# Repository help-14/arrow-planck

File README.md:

# RGB Planck
RGB Planck with arrow keys. This is a edited version of [regack's DrunkPlanck](https://geekhack.org/index.php?topic=79929.0) rev 0.6.

This should fit with all kind of case for planck.

##Layout

Support 2 arrow keys layout and three space keys layout.

[Layout 1](http://www.keyboard-layout-editor.com/#/gists/1d069f35c259fc881293490941ea733b)

[Layout 2](http://www.keyboard-layout-editor.com/#/gists/62a24cf77f6c1db29a28023afb4e101e)

[Layout 3](http://www.keyboard-layout-editor.com/#/gists/e7b004d03016d69c539ebc4d6f262bce)

Editing ...

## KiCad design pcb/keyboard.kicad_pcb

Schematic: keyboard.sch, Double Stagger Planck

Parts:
C1, C2: 22pf
C3, C4: 0.1uF; 0805
C7, C8: 1uF; 0805
G1: Graphic
H1, H2, H3, H4, H5, H6, H7, H8, H9, H10, H11, H12, H13, H14, H15: Hole
IC1: ATMEGA32U2; TQFP32
J1: USBMINI_B05
R1, R2: 22Ω; 0805
R3, R4: 10kΩ; 0805
S1: ADTSMW69NVTR; tactile_switch
X1: 7M-16.000MAAJ-T

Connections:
/Matrix/col1: IC1.6 ((OC.0B/INT0)PD0); also elsewhere on the board
/Matrix/col2: IC1.7 ((AIN0/INT1)PD1); also elsewhere on the board
/Matrix/col3: IC1.8 ((RXD1/AIN1/INT2)PD2); also elsewhere on the board
/Matrix/col4: IC1.9 ((TXD1/INT3)PD3); also elsewhere on the board
/Matrix/col5: IC1.10 ((INT5/AIN3)PD4); also elsewhere on the board
/Matrix/col6: IC1.11 ((XCK/AIN4/PCINT12)PD5); also elsewhere on the board
/Matrix/col7: IC1.12 ((~RTS~/AIN5/INT6)PD6); also elsewhere on the board
/Matrix/col8: IC1.22 ((INT4/ICP1/CLKO)PC7); also elsewhere on the board
/Matrix/col9: IC1.26 ((PCINT10)PC4); also elsewhere on the board
/Matrix/col10: IC1.5 ((PCINT11/AIN2)PC2); also elsewhere on the board
/Matrix/col11: IC1.14 ((~SS~/PCINT0)PB0); also elsewhere on the board
/Matrix/col12: IC1.15 ((SCLK/PCINT1)PB1); also elsewhere on the board
/Matrix/row1: IC1.17 ((PDO/MISO/PCINT3)PB3); also elsewhere on the board
/Matrix/row2: IC1.18 ((T1/PCINT4)PB4); also elsewhere on the board
/Matrix/row3: IC1.19 ((PCINT5)PB5); also elsewhere on the board
/Matrix/row4: IC1.20 ((PCINT6)PB6); also elsewhere on the board
/RGB/DIN: IC1.16 ((PDI/MOSI/PCINT2)PB2); also elsewhere on the board
GND: C1.2, C2.2, C3.2, C4.2, C7.2, C8.2, IC1.3 (GND), IC1.28 (UGnd), J1.5 (GND), R3.2, S1.1, X1.2, X1.4; also elsewhere on the board
unnamed: IC1.30 (D-), R1.1
unnamed: IC1.29 (D+), R2.1
unnamed: C8.1, IC1.27 (Ucap)
unnamed: IC1.13 ((~HWB~/AIN6/T0/INT7)PD7), R3.1
unnamed: IC1.24 (~RESET~(PC1/dW)), R4.2, S1.3
unnamed: J1.2 (D-), R1.2
unnamed: J1.3 (D+), R2.2
unnamed: C1.1, IC1.2 (XTAL2), X1.1
unnamed: C2.1, IC1.1 (XTAL1), X1.3
VCC: C3.1, C4.1, C7.1, IC1.4 (VCC), IC1.31 (UVcc), IC1.32 (AVCC), J1.1 (VBUS), R4.1; also elsewhere on the board

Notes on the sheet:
ATMEGA32U2 MCU Block
Reset Switch
Crystal
USB
CAPACITORS NEAR MCU
C7 NEAR USB
Double Stagger Planck Keyboard
pwm

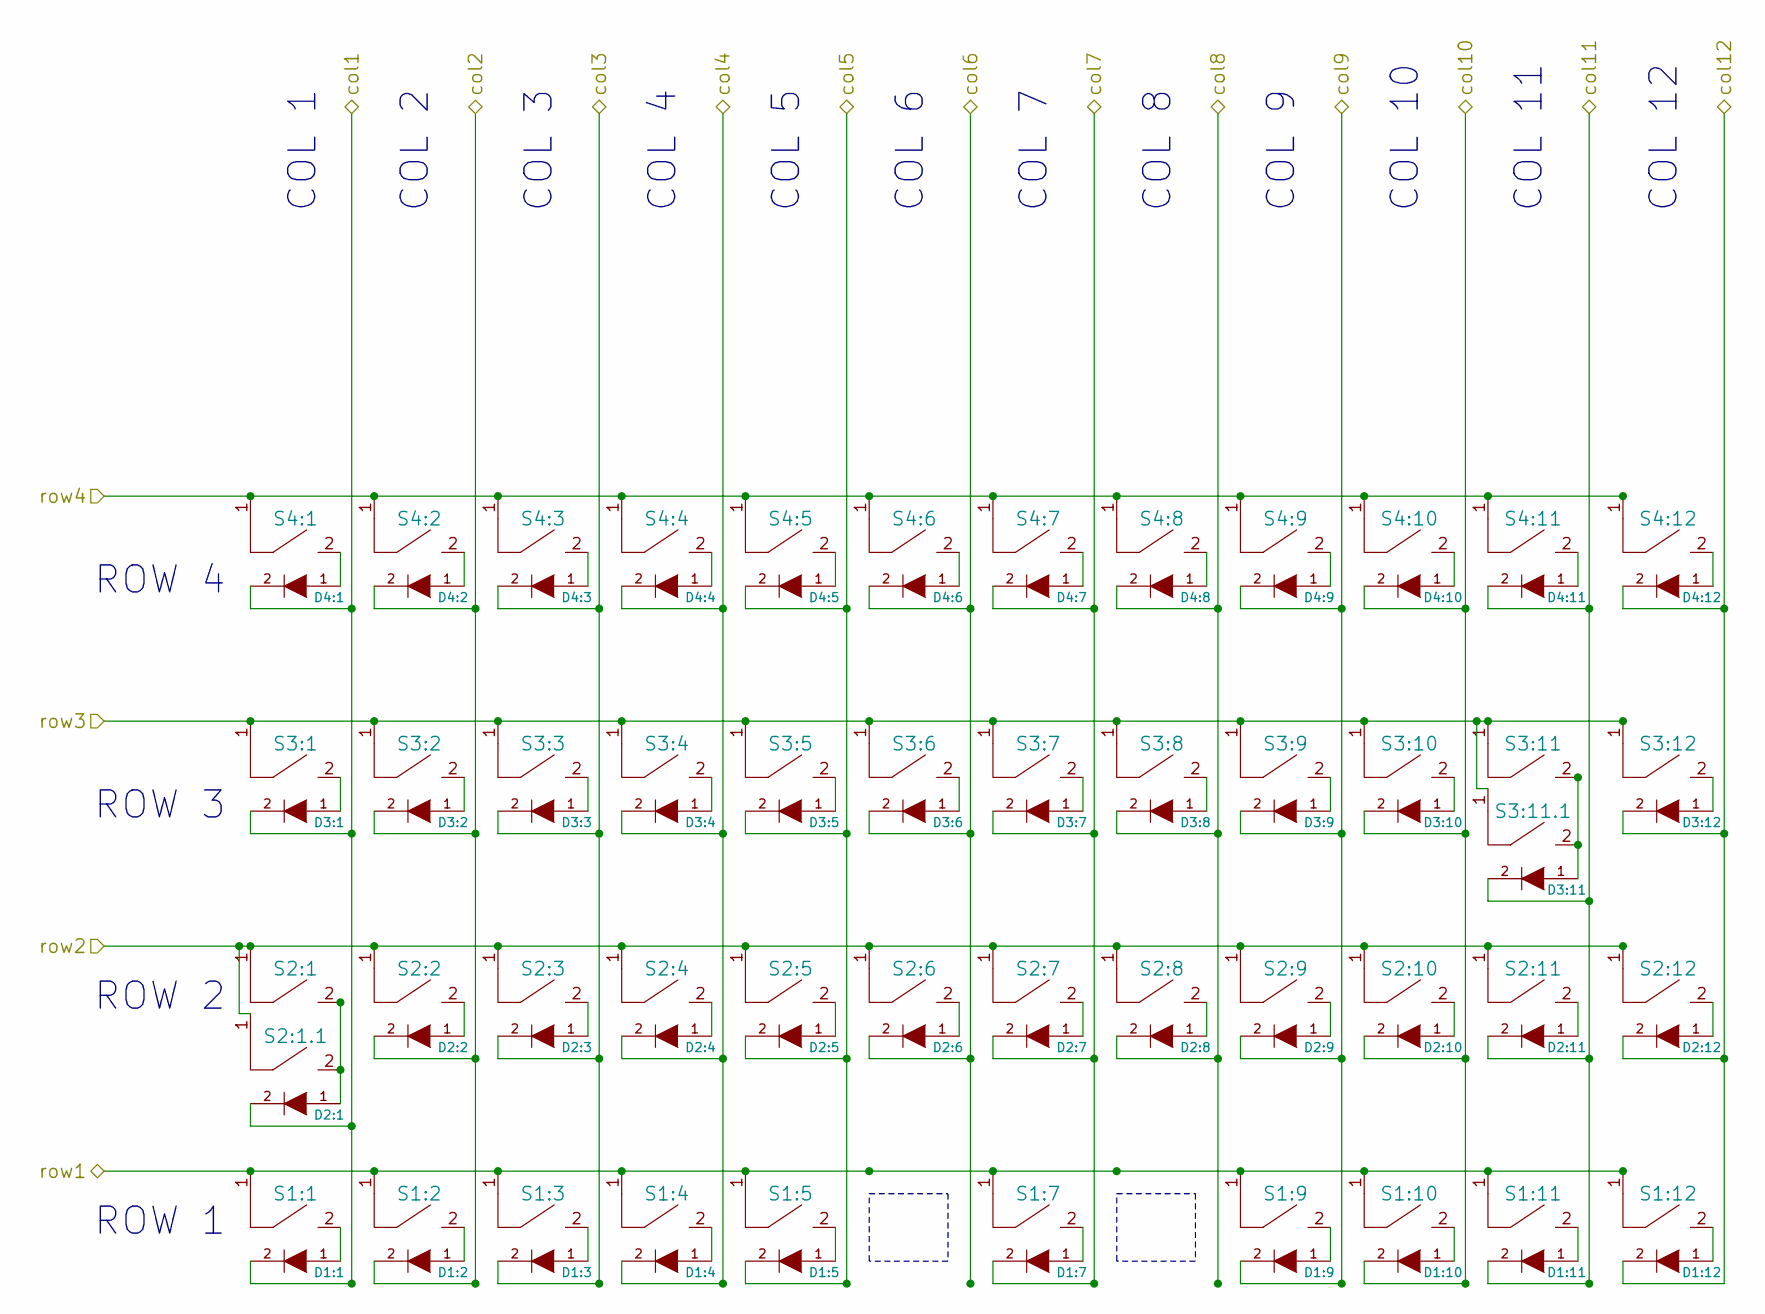
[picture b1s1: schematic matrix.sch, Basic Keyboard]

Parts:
D1:1, D1:2, D1:3, D1:4, D1:5, D1:7, D1:9, D1:10, D1:11, D1:12, D2:1, D2:2, D2:3, D2:4, D2:5, D2:6, D2:7, D2:8, D2:9, D2:10, D2:11, D2:12, D3:1, D3:2, D3:3, D3:4, D3:5, D3:6, D3:7, D3:8, D3:9, D3:10, D3:11, D3:12, D4:1, D4:2, D4:3, D4:4, D4:5, D4:6, D4:7, D4:8, D4:9, D4:10, D4:11, D4:12: 1N4148
S1:1, S1:2, S1:3, S1:4, S1:5, S1:7, S1:9, S1:10, S1:11, S1:12, S2:1, S2:1.1, S2:2, S2:3, S2:4, S2:5, S2:6, S2:7, S2:8, S2:9, S2:10, S2:11, S2:12, S3:1, S3:2, S3:3, S3:4, S3:5, S3:6, S3:7, S3:8, S3:9, S3:10, S3:11, S3:11.1, S3:12, S4:1, S4:2, S4:3, S4:4, S4:5, S4:6, S4:7, S4:8, S4:9, S4:10, S4:11, S4:12: MX1A

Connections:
/Matrix/col1: D1:1.2 (Cathode), D2:1.2 (Cathode), D3:1.2 (Cathode), D4:1.2 (Cathode); also elsewhere on the board
/Matrix/col2: D1:2.2 (Cathode), D2:2.2 (Cathode), D3:2.2 (Cathode), D4:2.2 (Cathode); also elsewhere on the board
/Matrix/col3: D1:3.2 (Cathode), D2:3.2 (Cathode), D3:3.2 (Cathode), D4:3.2 (Cathode); also elsewhere on the board
/Matrix/col4: D1:4.2 (Cathode), D2:4.2 (Cathode), D3:4.2 (Cathode), D4:4.2 (Cathode); also elsewhere on the board
/Matrix/col5: D1:5.2 (Cathode), D2:5.2 (Cathode), D3:5.2 (Cathode), D4:5.2 (Cathode); also elsewhere on the board
/Matrix/col6: D2:6.2 (Cathode), D3:6.2 (Cathode), D4:6.2 (Cathode); also elsewhere on the board
/Matrix/col7: D1:7.2 (Cathode), D2:7.2 (Cathode), D3:7.2 (Cathode), D4:7.2 (Cathode); also elsewhere on the board
/Matrix/col8: D2:8.2 (Cathode), D3:8.2 (Cathode), D4:8.2 (Cathode); also elsewhere on the board
/Matrix/col9: D1:9.2 (Cathode), D2:9.2 (Cathode), D3:9.2 (Cathode), D4:9.2 (Cathode); also elsewhere on the board
/Matrix/col10: D1:10.2 (Cathode), D2:10.2 (Cathode), D3:10.2 (Cathode), D4:10.2 (Cathode); also elsewhere on the board
/Matrix/col11: D1:11.2 (Cathode), D2:11.2 (Cathode), D3:11.2 (Cathode), D4:11.2 (Cathode); also elsewhere on the board
/Matrix/col12: D1:12.2 (Cathode), D2:12.2 (Cathode), D3:12.2 (Cathode), D4:12.2 (Cathode); also elsewhere on the board
/Matrix/row1: S1:1.1, S1:2.1, S1:3.1, S1:4.1, S1:5.1, S1:7.1, S1:9.1, S1:10.1, S1:11.1, S1:12.1; also elsewhere on the board
/Matrix/row2: S2:1.1, S2:1.1.1, S2:2.1, S2:3.1, S2:4.1, S2:5.1, S2:6.1, S2:7.1, S2:8.1, S2:9.1, S2:10.1, S2:11.1, S2:12.1; also elsewhere on the board
/Matrix/row3: S3:1.1, S3:2.1, S3:3.1, S3:4.1, S3:5.1, S3:6.1, S3:7.1, S3:8.1, S3:9.1, S3:10.1, S3:11.1, S3:11.1.1, S3:12.1; also elsewhere on the board
/Matrix/row4: S4:1.1, S4:2.1, S4:3.1, S4:4.1, S4:5.1, S4:6.1, S4:7.1, S4:8.1, S4:9.1, S4:10.1, S4:11.1, S4:12.1; also elsewhere on the board
unnamed: D4:9.1 (Anode), S4:9.2
unnamed: D3:10.1 (Anode), S3:10.2
unnamed: D4:10.1 (Anode), S4:10.2
unnamed: D4:11.1 (Anode), S4:11.2
unnamed 31: D2:11.1 (Anode), S2:11.2; also elsewhere on the board
unnamed 32: D2:10.1 (Anode), S2:10.2; also elsewhere on the board
unnamed: D1:11.1 (Anode), S1:11.2
unnamed: D2:9.1 (Anode), S2:9.2
unnamed: D3:9.1 (Anode), S3:9.2
unnamed: D4:8.1 (Anode), S4:8.2
unnamed: D4:7.1 (Anode), S4:7.2
unnamed: D4:5.1 (Anode), S4:5.2
unnamed: D4:4.1 (Anode), S4:4.2
unnamed: D3:4.1 (Anode), S3:4.2
unnamed: D2:4.1 (Anode), S2:4.2
unnamed: D4:6.1 (Anode), S4:6.2
unnamed: D3:6.1 (Anode), S3:6.2
unnamed: D2:5.1 (Anode), S2:5.2
unnamed: D3:8.1 (Anode), S3:8.2
unnamed: D2:8.1 (Anode), S2:8.2
unnamed: D2:7.1 (Anode), S2:7.2
unnamed: D3:7.1 (Anode), S3:7.2
unnamed: D3:5.1 (Anode), S3:5.2
unnamed: D1:1.1 (Anode), S1:1.2
unnamed: D1:10.1 (Anode), S1:10.2
unnamed: D3:12.1 (Anode), S3:12.2
unnamed: D4:12.1 (Anode), S4:12.2
unnamed 54: D2:12.1 (Anode), S2:12.2; also elsewhere on the board
unnamed: D2:1.1 (Anode), S2:1.2, S2:1.1.2
unnamed: D3:11.1 (Anode), S3:11.2, S3:11.1.2
unnamed: D3:1.1 (Anode), S3:1.2
unnamed 58: D1:9.1 (Anode), S1:9.2; also elsewhere on the board
unnamed: D1:12.1 (Anode), S1:12.2
unnamed: D1:5.1 (Anode), S1:5.2
unnamed: D1:4.1 (Anode), S1:4.2
unnamed: D4:1.1 (Anode), S4:1.2
unnamed: D3:3.1 (Anode), S3:3.2
unnamed: D3:2.1 (Anode), S3:2.2
unnamed: D2:6.1 (Anode), S2:6.2
unnamed: D1:7.1 (Anode), S1:7.2
unnamed: D1:3.1 (Anode), S1:3.2
unnamed: D1:2.1 (Anode), S1:2.2
unnamed: D2:3.1 (Anode), S2:3.2
unnamed: D2:2.1 (Anode), S2:2.2
unnamed: D4:3.1 (Anode), S4:3.2
unnamed: D4:2.1 (Anode), S4:2.2

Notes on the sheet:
ROW 1
ROW 2
ROW 3
ROW 4
COL 1
COL 2
COL 3
COL 4
COL 5
COL 6
COL 7
COL 8
COL 9
COL 10
COL 11
COL 12

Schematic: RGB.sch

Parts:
C1:1, C1:2, C1:3, C1:4, C1:5, C1:7, C1:9, C1:10, C1:11, C1:12, C2:1, C2:2, C2:3, C2:4, C2:5, C2:6, C2:7, C2:8, C2:9, C2:10, C2:11, C2:12, C3:1, C3:2, C3:3, C3:4, C3:5, C3:6, C3:7, C3:8, C3:9, C3:10, C3:11, C3:12, C4:1, C4:2, C4:3, C4:4, C4:5, C4:6, C4:7, C4:8, C4:9, C4:10, C4:11, C4:12: 0.1uF 50v
IC1:1, IC1:2, IC1:3, IC1:4, IC1:5, IC1:7, IC1:9, IC1:10, IC1:11, IC1:12, IC2:1, IC2:2, IC2:3, IC2:4, IC2:5, IC2:6, IC2:7, IC2:8, IC2:9, IC2:10, IC2:11, IC2:12, IC3:1, IC3:2, IC3:3, IC3:4, IC3:5, IC3:6, IC3:7, IC3:8, IC3:9, IC3:10, IC3:11, IC3:12, IC4:1, IC4:2, IC4:3, IC4:4, IC4:5, IC4:6, IC4:7, IC4:8, IC4:9, IC4:10, IC4:11, IC4:12: WS2811
L1:1, L1:2, L1:3, L1:4, L1:5, L1:7, L1:9, L1:10, L1:11, L1:12, L2:1, L2:1.1, L2:2, L2:3, L2:4, L2:5, L2:6, L2:7, L2:8, L2:9, L2:10, L2:11, L2:12, L3:1, L3:2, L3:3, L3:4, L3:5, L3:6, L3:7, L3:8, L3:9, L3:10, L3:11, L3:11.1, L3:12, L4:1, L4:2, L4:3, L4:4, L4:5, L4:6, L4:7, L4:8, L4:9, L4:10, L4:11, L4:12: 0606_RGB_LED
R1:1, R1:2, R1:3, R1:4, R1:5, R1:7, R1:9, R1:10, R1:11, R1:12, R2:1, R2:2, R2:3, R2:4, R2:5, R2:6, R2:7, R2:8, R2:9, R2:10, R2:11, R2:12, R3:1, R3:2, R3:3, R3:4, R3:5, R3:6, R3:7, R3:8, R3:9, R3:10, R3:11, R3:12, R4:1, R4:2, R4:3, R4:4, R4:5, R4:6, R4:7, R4:8, R4:9, R4:10, R4:11, R4:12: 100
RBL1: 33

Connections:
/RGB/DIN: RBL1.2; also elsewhere on the board
GND: C1:1.2, C1:2.2, C1:3.2, C1:4.2, C1:5.2, C1:7.2, C1:9.2, C1:10.2, C1:11.2, C1:12.2, C2:1.2, C2:2.2, C2:3.2, C2:4.2, C2:5.2, C2:6.2, C2:7.2, C2:8.2, C2:9.2, C2:10.2, C2:11.2, C2:12.2, C3:1.2, C3:2.2, C3:3.2, C3:4.2, C3:5.2, C3:6.2, C3:7.2, C3:8.2, C3:9.2, C3:10.2, C3:11.2, C3:12.2, C4:1.2, C4:2.2, C4:3.2, C4:4.2, C4:5.2, C4:6.2, C4:7.2, C4:8.2, C4:9.2, C4:10.2, C4:11.2, C4:12.2, IC1:1.4 (GND), IC1:2.4 (GND), IC1:3.4 (GND), IC1:4.4 (GND), IC1:5.4 (GND), IC1:7.4 (GND), IC1:9.4 (GND), IC1:10.4 (GND), IC1:11.4 (GND), IC1:12.4 (GND), IC2:1.4 (GND), IC2:2.4 (GND), IC2:3.4 (GND), IC2:4.4 (GND), IC2:5.4 (GND), IC2:6.4 (GND), IC2:7.4 (GND), IC2:8.4 (GND), IC2:9.4 (GND), IC2:10.4 (GND), IC2:11.4 (GND), IC2:12.4 (GND), IC3:1.4 (GND), IC3:2.4 (GND), IC3:3.4 (GND), IC3:4.4 (GND), IC3:5.4 (GND), IC3:6.4 (GND), IC3:7.4 (GND), IC3:8.4 (GND), IC3:9.4 (GND), IC3:10.4 (GND), IC3:11.4 (GND), IC3:12.4 (GND), IC4:1.4 (GND), IC4:2.4 (GND), IC4:3.4 (GND), IC4:4.4 (GND), IC4:5.4 (GND), IC4:6.4 (GND), IC4:7.4 (GND), IC4:8.4 (GND), IC4:9.4 (GND), IC4:10.4 (GND), IC4:11.4 (GND), IC4:12.4 (GND); also elsewhere on the board
unnamed: IC4:10.2 (OutG), L4:10.2 (G)
unnamed: IC4:10.3 (OutB), L4:10.3 (B)
unnamed: IC4:10.1 (OutR), L4:10.1 (R)
unnamed: IC1:9.5 (Dout), IC4:10.6 (Din)
unnamed: C4:10.1, IC4:10.8 (Vcc), R4:10.1
unnamed: IC3:9.6 (Din), IC4:9.5 (Dout)
unnamed: IC2:9.6 (Din), IC3:9.5 (Dout)
unnamed: IC3:10.2 (OutG), L3:10.2 (G)
unnamed: IC3:10.6 (Din), IC4:10.5 (Dout)
unnamed: IC2:10.6 (Din), IC3:10.5 (Dout)
unnamed: IC3:10.3 (OutB), L3:10.3 (B)
unnamed: IC3:10.1 (OutR), L3:10.1 (R)
unnamed: C3:10.1, IC3:10.8 (Vcc), R3:10.1
unnamed: IC1:9.6 (Din), IC2:9.5 (Dout)
unnamed: C1:9.1, IC1:9.8 (Vcc), R1:9.1
unnamed 88: IC1:9.3 (OutB), L1:9.3 (B); also elsewhere on the board
unnamed 89: IC1:9.2 (OutG), L1:9.2 (G); also elsewhere on the board
unnamed 90: IC1:9.1 (OutR), L1:9.1 (R); also elsewhere on the board
unnamed: IC4:11.2 (OutG), L4:11.2 (G)
unnamed: C4:9.1, IC4:9.8 (Vcc), R4:9.1
unnamed: C2:9.1, IC2:9.8 (Vcc), R2:9.1
unnamed: C3:9.1, IC3:9.8 (Vcc), R3:9.1
unnamed: C2:10.1, IC2:10.8 (Vcc), R2:10.1
unnamed: IC1:10.6 (Din), IC2:10.5 (Dout)
unnamed: IC4:11.1 (OutR), L4:11.1 (R)
unnamed: IC4:11.3 (OutB), L4:11.3 (B)
unnamed: IC1:10.5 (Dout), IC4:11.6 (Din)
unnamed: C1:10.1, IC1:10.8 (Vcc), R1:10.1
unnamed: IC2:10.2 (OutG), L2:10.2 (G)
unnamed: IC2:10.3 (OutB), L2:10.3 (B)
unnamed: IC2:10.1 (OutR), L2:10.1 (R)
unnamed: IC1:10.1 (OutR), L1:10.1 (R)
unnamed: IC1:10.3 (OutB), L1:10.3 (B)
unnamed: IC1:10.2 (OutG), L1:10.2 (G)
unnamed: IC3:8.2 (OutG), L3:8.2 (G)
unnamed: IC3:8.3 (OutB), L3:8.3 (B)
unnamed: IC3:8.1 (OutR), L3:8.1 (R)
unnamed: C3:8.1, IC3:8.8 (Vcc), R3:8.1
unnamed: IC2:8.3 (OutB), L2:8.3 (B)
unnamed: C2:8.1, IC2:8.8 (Vcc), R2:8.1
unnamed: IC2:8.6 (Din), IC3:8.5 (Dout)
unnamed: IC2:8.2 (OutG), L2:8.2 (G)
unnamed: IC2:8.1 (OutR), L2:8.1 (R)
unnamed: C3:7.1, IC3:7.8 (Vcc), R3:7.1
unnamed: IC1:7.5 (Dout), IC4:8.6 (Din)
unnamed: IC3:7.6 (Din), IC4:7.5 (Dout)
unnamed: IC2:7.6 (Din), IC3:7.5 (Dout)
unnamed: C2:7.1, IC2:7.8 (Vcc), R2:7.1
unnamed: C4:7.1, IC4:7.8 (Vcc), R4:7.1
unnamed: IC1:7.6 (Din), IC2:7.5 (Dout)
unnamed: IC4:8.3 (OutB), L4:8.3 (B)
unnamed: C4:8.1, IC4:8.8 (Vcc), R4:8.1
unnamed: IC3:8.6 (Din), IC4:8.5 (Dout)
unnamed: IC4:8.2 (OutG), L4:8.2 (G)
unnamed: IC4:8.1 (OutR), L4:8.1 (R)
unnamed: IC3:9.3 (OutB), L3:9.3 (B)
unnamed: IC3:9.2 (OutG), L3:9.2 (G)
unnamed: IC3:9.1 (OutR), L3:9.1 (R)
unnamed: IC2:9.3 (OutB), L2:9.3 (B)
unnamed: IC2:9.2 (OutG), L2:9.2 (G)
unnamed: IC2:9.1 (OutR), L2:9.1 (R)
unnamed: IC2:8.5 (Dout), IC4:9.6 (Din)
unnamed: IC4:9.3 (OutB), L4:9.3 (B)
unnamed: IC4:9.2 (OutG), L4:9.2 (G)
unnamed: IC4:9.1 (OutR), L4:9.1 (R)
unnamed: IC2:6.5 (Dout), IC4:7.6 (Din)
unnamed: IC3:12.6 (Din), IC4:12.5 (Dout)
unnamed: C1:3.1, IC1:3.8 (Vcc), R1:3.1
unnamed: IC1:3.2 (OutG), L1:3.2 (G)
unnamed: IC1:3.1 (OutR), L1:3.1 (R)
unnamed: IC1:3.3 (OutB), L1:3.3 (B)
unnamed: IC2:12.6 (Din), IC3:12.5 (Dout)
unnamed: IC1:11.5 (Dout), IC4:12.6 (Din)
unnamed: IC1:12.6 (Din), IC2:12.5 (Dout)
unnamed: C1:12.1, IC1:12.8 (Vcc), R1:12.1
unnamed: IC1:12.3 (OutB), L1:12.3 (B)
unnamed: IC1:12.2 (OutG), L1:12.2 (G)
unnamed: IC1:12.1 (OutR), L1:12.1 (R)
unnamed: C2:12.1, IC2:12.8 (Vcc), R2:12.1
unnamed: C4:12.1, IC4:12.8 (Vcc), R4:12.1
unnamed: C3:12.1, IC3:12.8 (Vcc), R3:12.1
unnamed: IC2:1.3 (OutB), L2:1.3 (B), L2:1.1.3 (B)
unnamed: IC2:1.2 (OutG), L2:1.2 (G), L2:1.1.2 (G)
unnamed: IC2:1.1 (OutR), L2:1.1 (R), L2:1.1.1 (R)
unnamed: IC3:6.3 (OutB), L3:6.3 (B)
unnamed: IC3:6.2 (OutG), L3:6.2 (G)
unnamed: IC3:6.1 (OutR), L3:6.1 (R)
unnamed: IC3:11.2 (OutG), L3:11.2 (G), L3:11.1.2 (G)
unnamed: IC3:11.3 (OutB), L3:11.3 (B), L3:11.1.3 (B)
unnamed: IC3:11.1 (OutR), L3:11.1 (R), L3:11.1.1 (R)
unnamed: IC1:2.1 (OutR), L1:2.1 (R)
unnamed: IC1:2.2 (OutG), L1:2.2 (G)
unnamed: IC1:3.6 (Din), IC2:3.5 (Dout)
unnamed: C1:2.1, IC1:2.8 (Vcc), R1:2.1
unnamed: IC1:2.5 (Dout), IC4:3.6 (Din)
unnamed: IC1:2.3 (OutB), L1:2.3 (B)
unnamed: IC1:11.1 (OutR), L1:11.1 (R)
unnamed: IC1:11.3 (OutB), L1:11.3 (B)
unnamed: IC1:11.2 (OutG), L1:11.2 (G)
unnamed: IC1:11.6 (Din), IC2:11.5 (Dout)
unnamed: IC2:11.3 (OutB), L2:11.3 (B)
unnamed: IC2:11.2 (OutG), L2:11.2 (G)
unnamed: C1:11.1, IC1:11.8 (Vcc), R1:11.1
unnamed: C4:11.1, IC4:11.8 (Vcc), R4:11.1
unnamed: IC2:11.1 (OutR), L2:11.1 (R)
unnamed: C2:11.1, IC2:11.8 (Vcc), R2:11.1
unnamed: C3:11.1, IC3:11.8 (Vcc), R3:11.1
unnamed: IC3:11.6 (Din), IC4:11.5 (Dout)
unnamed: IC2:11.6 (Din), IC3:11.5 (Dout)
unnamed: IC3:12.3 (OutB), L3:12.3 (B)
unnamed: IC3:12.2 (OutG), L3:12.2 (G)
unnamed: IC3:12.1 (OutR), L3:12.1 (R)
unnamed: IC2:12.3 (OutB), L2:12.3 (B)
unnamed: IC2:12.2 (OutG), L2:12.2 (G)
unnamed: IC2:12.1 (OutR), L2:12.1 (R)
unnamed: IC4:12.3 (OutB), L4:12.3 (B)
unnamed: IC4:12.2 (OutG), L4:12.2 (G)
unnamed: IC4:12.1 (OutR), L4:12.1 (R)
unnamed: C1:4.1, IC1:4.8 (Vcc), R1:4.1
unnamed: IC3:2.6 (Din), IC4:2.5 (Dout)
unnamed: IC2:2.6 (Din), IC3:2.5 (Dout)
unnamed: C2:2.1, IC2:2.8 (Vcc), R2:2.1
unnamed: C4:2.1, IC4:2.8 (Vcc), R4:2.1
unnamed: C3:2.1, IC3:2.8 (Vcc), R3:2.1
unnamed: C3:3.1, IC3:3.8 (Vcc), R3:3.1
unnamed: C4:3.1, IC4:3.8 (Vcc), R4:3.1
unnamed: IC4:3.3 (OutB), L4:3.3 (B)
unnamed: IC4:3.2 (OutG), L4:3.2 (G)
unnamed: IC4:3.1 (OutR), L4:3.1 (R)
unnamed: IC1:4.1 (OutR), L1:4.1 (R)
unnamed: IC1:4.3 (OutB), L1:4.3 (B)
unnamed: IC1:4.2 (OutG), L1:4.2 (G)
unnamed: IC1:2.6 (Din), IC2:2.5 (Dout)
unnamed: IC2:2.3 (OutB), L2:2.3 (B)
unnamed: IC1:5.6 (Din), IC2:5.5 (Dout)
unnamed: C1:5.1, IC1:5.8 (Vcc), R1:5.1
unnamed: IC1:5.3 (OutB), L1:5.3 (B)
unnamed: IC1:5.2 (OutG), L1:5.2 (G)
unnamed: IC1:5.1 (OutR), L1:5.1 (R)
unnamed: IC2:3.6 (Din), IC3:3.5 (Dout)
unnamed: C2:3.1, IC2:3.8 (Vcc), R2:3.1
unnamed: IC3:3.6 (Din), IC4:3.5 (Dout)
unnamed: IC3:3.3 (OutB), L3:3.3 (B)
unnamed: IC3:3.2 (OutG), L3:3.2 (G)
unnamed: IC3:3.1 (OutR), L3:3.1 (R)
unnamed: IC2:2.2 (OutG), L2:2.2 (G)
unnamed: IC2:3.3 (OutB), L2:3.3 (B)
unnamed: IC2:3.2 (OutG), L2:3.2 (G)
unnamed: IC2:3.1 (OutR), L2:3.1 (R)
unnamed: C2:1.1, IC2:1.8 (Vcc), R2:1.1
unnamed: IC1:1.3 (OutB), L1:1.3 (B)
unnamed: IC1:1.6 (Din), IC2:1.5 (Dout)
unnamed: IC1:1.2 (OutG), L1:1.2 (G)
unnamed: IC1:1.1 (OutR), L1:1.1 (R)
unnamed: C1:1.1, IC1:1.8 (Vcc), R1:1.1
unnamed: IC4:1.3 (OutB), L4:1.3 (B)
unnamed: IC4:1.2 (OutG), L4:1.2 (G)
unnamed: IC4:1.1 (OutR), L4:1.1 (R)
unnamed: C4:1.1, IC4:1.8 (Vcc), R4:1.1
unnamed: IC4:1.6 (Din), RBL1.1
unnamed: IC3:1.3 (OutB), L3:1.3 (B)
unnamed: IC3:1.6 (Din), IC4:1.5 (Dout)
unnamed: IC2:1.6 (Din), IC3:1.5 (Dout)
unnamed: IC3:1.2 (OutG), L3:1.2 (G)
unnamed: IC3:1.1 (OutR), L3:1.1 (R)
unnamed: C3:1.1, IC3:1.8 (Vcc), R3:1.1
unnamed: IC3:2.2 (OutG), L3:2.2 (G)
unnamed: IC3:2.1 (OutR), L3:2.1 (R)
unnamed: IC3:2.3 (OutB), L3:2.3 (B)
unnamed: IC1:1.5 (Dout), IC4:2.6 (Din)
unnamed: IC2:2.1 (OutR), L2:2.1 (R)
unnamed: IC4:2.3 (OutB), L4:2.3 (B)
unnamed: IC4:2.2 (OutG), L4:2.2 (G)
unnamed: IC4:2.1 (OutR), L4:2.1 (R)
unnamed: C3:6.1, IC3:6.8 (Vcc), R3:6.1
unnamed: IC1:5.5 (Dout), IC4:6.6 (Din)
unnamed: IC3:6.6 (Din), IC4:6.5 (Dout)
unnamed: IC2:6.6 (Din), IC3:6.5 (Dout)
unnamed: IC2:6.3 (OutB), L2:6.3 (B)
unnamed: IC2:6.2 (OutG), L2:6.2 (G)
unnamed: IC2:6.1 (OutR), L2:6.1 (R)
unnamed: C2:6.1, IC2:6.8 (Vcc), R2:6.1
unnamed: C4:5.1, IC4:5.8 (Vcc), R4:5.1
unnamed: C2:5.1, IC2:5.8 (Vcc), R2:5.1
unnamed: C3:5.1, IC3:5.8 (Vcc), R3:5.1
unnamed: IC4:6.3 (OutB), L4:6.3 (B)
unnamed: IC4:6.2 (OutG), L4:6.2 (G)
unnamed: IC4:6.1 (OutR), L4:6.1 (R)
unnamed: C4:6.1, IC4:6.8 (Vcc), R4:6.1
unnamed: IC3:5.6 (Din), IC4:5.5 (Dout)
unnamed: IC2:5.6 (Din), IC3:5.5 (Dout)
unnamed: C1:7.1, IC1:7.8 (Vcc), R1:7.1
unnamed: IC3:7.1 (OutR), L3:7.1 (R)
unnamed: IC3:7.3 (OutB), L3:7.3 (B)
unnamed: IC3:7.2 (OutG), L3:7.2 (G)
unnamed: IC2:7.2 (OutG), L2:7.2 (G)
unnamed: IC2:7.3 (OutB), L2:7.3 (B)
unnamed: IC2:7.1 (OutR), L2:7.1 (R)
unnamed: IC4:7.2 (OutG), L4:7.2 (G)
unnamed: IC4:7.3 (OutB), L4:7.3 (B)
unnamed: IC4:7.1 (OutR), L4:7.1 (R)
unnamed: IC2:4.1 (OutR), L2:4.1 (R)
unnamed: IC1:4.6 (Din), IC2:4.5 (Dout)
unnamed: IC2:4.3 (OutB), L2:4.3 (B)
unnamed: IC2:4.2 (OutG), L2:4.2 (G)
unnamed: C2:4.1, IC2:4.8 (Vcc), R2:4.1
unnamed: C4:4.1, IC4:4.8 (Vcc), R4:4.1
unnamed: C3:4.1, IC3:4.8 (Vcc), R3:4.1
unnamed: IC4:4.1 (OutR), L4:4.1 (R)
unnamed: IC1:3.5 (Dout), IC4:4.6 (Din)
unnamed: IC4:4.3 (OutB), L4:4.3 (B)
unnamed: IC4:4.2 (OutG), L4:4.2 (G)
unnamed: IC3:4.1 (OutR), L3:4.1 (R)
unnamed: IC3:4.6 (Din), IC4:4.5 (Dout)
unnamed: IC2:4.6 (Din), IC3:4.5 (Dout)
unnamed: IC3:4.3 (OutB), L3:4.3 (B)
unnamed: IC3:4.2 (OutG), L3:4.2 (G)
unnamed: IC2:5.2 (OutG), L2:5.2 (G)
unnamed: IC2:5.3 (OutB), L2:5.3 (B)
unnamed: IC2:5.1 (OutR), L2:5.1 (R)
unnamed: IC1:7.2 (OutG), L1:7.2 (G)
unnamed: IC1:7.3 (OutB), L1:7.3 (B)
unnamed: IC1:7.1 (OutR), L1:7.1 (R)
unnamed: IC4:5.3 (OutB), L4:5.3 (B)
unnamed: IC1:4.5 (Dout), IC4:5.6 (Din)
unnamed: IC4:5.2 (OutG), L4:5.2 (G)
unnamed: IC4:5.1 (OutR), L4:5.1 (R)
unnamed: IC3:5.2 (OutG), L3:5.2 (G)
unnamed: IC3:5.3 (OutB), L3:5.3 (B)
unnamed: IC3:5.1 (OutR), L3:5.1 (R)
VCC: L1:1.4 (Vcc), L1:2.4 (Vcc), L1:3.4 (Vcc), L1:4.4 (Vcc), L1:5.4 (Vcc), L1:7.4 (Vcc), L1:9.4 (Vcc), L1:10.4 (Vcc), L1:11.4 (Vcc), L1:12.4 (Vcc), L2:1.4 (Vcc), L2:1.1.4 (Vcc), L2:2.4 (Vcc), L2:3.4 (Vcc), L2:4.4 (Vcc), L2:5.4 (Vcc), L2:6.4 (Vcc), L2:7.4 (Vcc), L2:8.4 (Vcc), L2:9.4 (Vcc), L2:10.4 (Vcc), L2:11.4 (Vcc), L2:12.4 (Vcc), L3:1.4 (Vcc), L3:2.4 (Vcc), L3:3.4 (Vcc), L3:4.4 (Vcc), L3:5.4 (Vcc), L3:6.4 (Vcc), L3:7.4 (Vcc), L3:8.4 (Vcc), L3:9.4 (Vcc), L3:10.4 (Vcc), L3:11.4 (Vcc), L3:11.1.4 (Vcc), L3:12.4 (Vcc), L4:1.4 (Vcc), L4:2.4 (Vcc), L4:3.4 (Vcc), L4:4.4 (Vcc), L4:5.4 (Vcc), L4:6.4 (Vcc), L4:7.4 (Vcc), L4:8.4 (Vcc), L4:9.4 (Vcc), L4:10.4 (Vcc), L4:11.4 (Vcc), L4:12.4 (Vcc), R1:1.2, R1:2.2, R1:3.2, R1:4.2, R1:5.2, R1:7.2, R1:9.2, R1:10.2, R1:11.2, R1:12.2, R2:1.2, R2:2.2, R2:3.2, R2:4.2, R2:5.2, R2:6.2, R2:7.2, R2:8.2, R2:9.2, R2:10.2, R2:11.2, R2:12.2, R3:1.2, R3:2.2, R3:3.2, R3:4.2, R3:5.2, R3:6.2, R3:7.2, R3:8.2, R3:9.2, R3:10.2, R3:11.2, R3:12.2, R4:1.2, R4:2.2, R4:3.2, R4:4.2, R4:5.2, R4:6.2, R4:7.2, R4:8.2, R4:9.2, R4:10.2, R4:11.2, R4:12.2; also elsewhere on the board

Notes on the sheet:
ROW 4
ROW 3
ROW 2
ROW 1
COL 1
COL 2
COL 3
COL 4
COL 5
COL 6
COL 7
COL 8
COL 9
COL 10
COL 11
COL 12
NO SWITCH

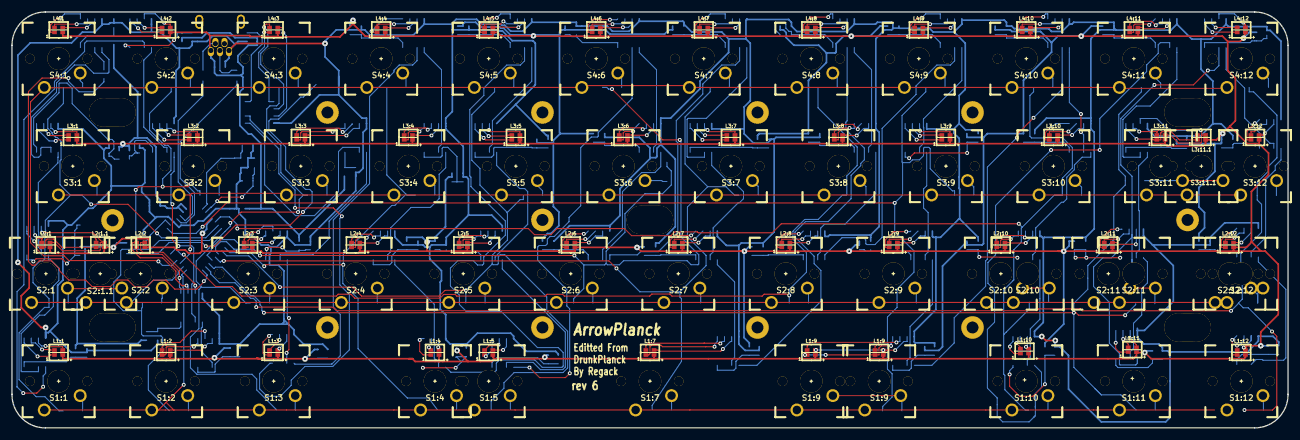
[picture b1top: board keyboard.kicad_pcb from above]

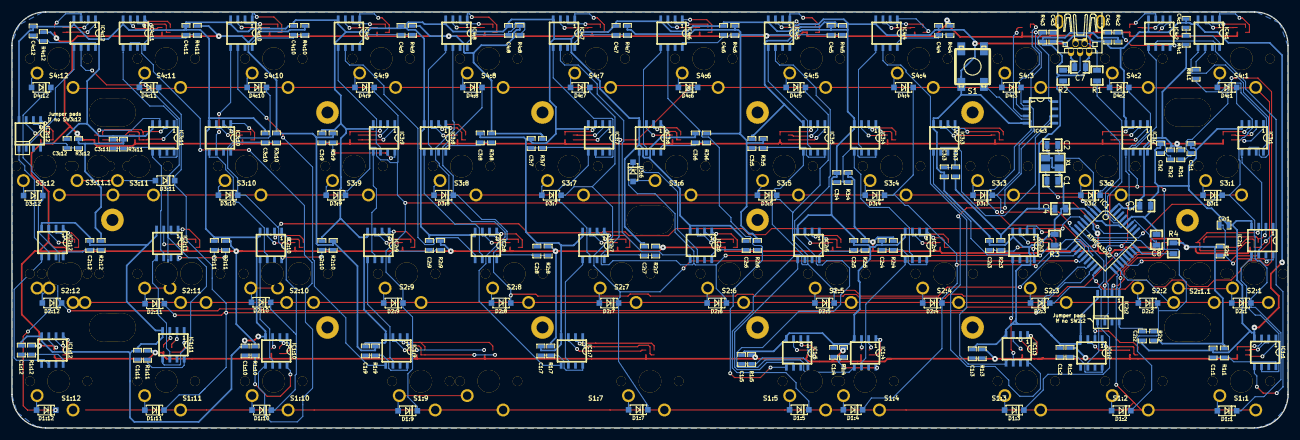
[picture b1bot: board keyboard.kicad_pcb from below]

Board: 2 copper layers, 225.5 x 73.5 mm, 326 parts (199 on the bottom side), 304 nets.

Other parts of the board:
H1.1, H1.2, H2.1, H2.2, H3.1, H3.2, H4.1, H4.2, H5.1, H5.2, H16: HOLE; Mechanical_Hole
L1:9#2: 0606_RGB_LED; CHERRY_MX_RGBLED
S1:9#2, S2:12#2: MX1A; CHERRY_PCB_125H_PlatedTH
S2:10#2, S2:11#2: MX1A; CHERRY_PCB_100H_PlatedTH

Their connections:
/Matrix/row1: S1:9#2.1; also elsewhere on the board
/Matrix/row2: S2:10#2.1, S2:11#2.1, S2:12#2.1; also elsewhere on the board
unnamed 31: S2:11#2.2; also elsewhere on the board
unnamed 32: S2:10#2.2; also elsewhere on the board
unnamed 54: S2:12#2.2; also elsewhere on the board
unnamed 58: S1:9#2.2; also elsewhere on the board
unnamed 88: L1:9#2.3; also elsewhere on the board
unnamed 89: L1:9#2.2; also elsewhere on the board
unnamed 90: L1:9#2.1; also elsewhere on the board
VCC: L1:9#2.4; also elsewhere on the board

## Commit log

2016-12-19 add pcb
2016-12-20 add arrow keys layout
